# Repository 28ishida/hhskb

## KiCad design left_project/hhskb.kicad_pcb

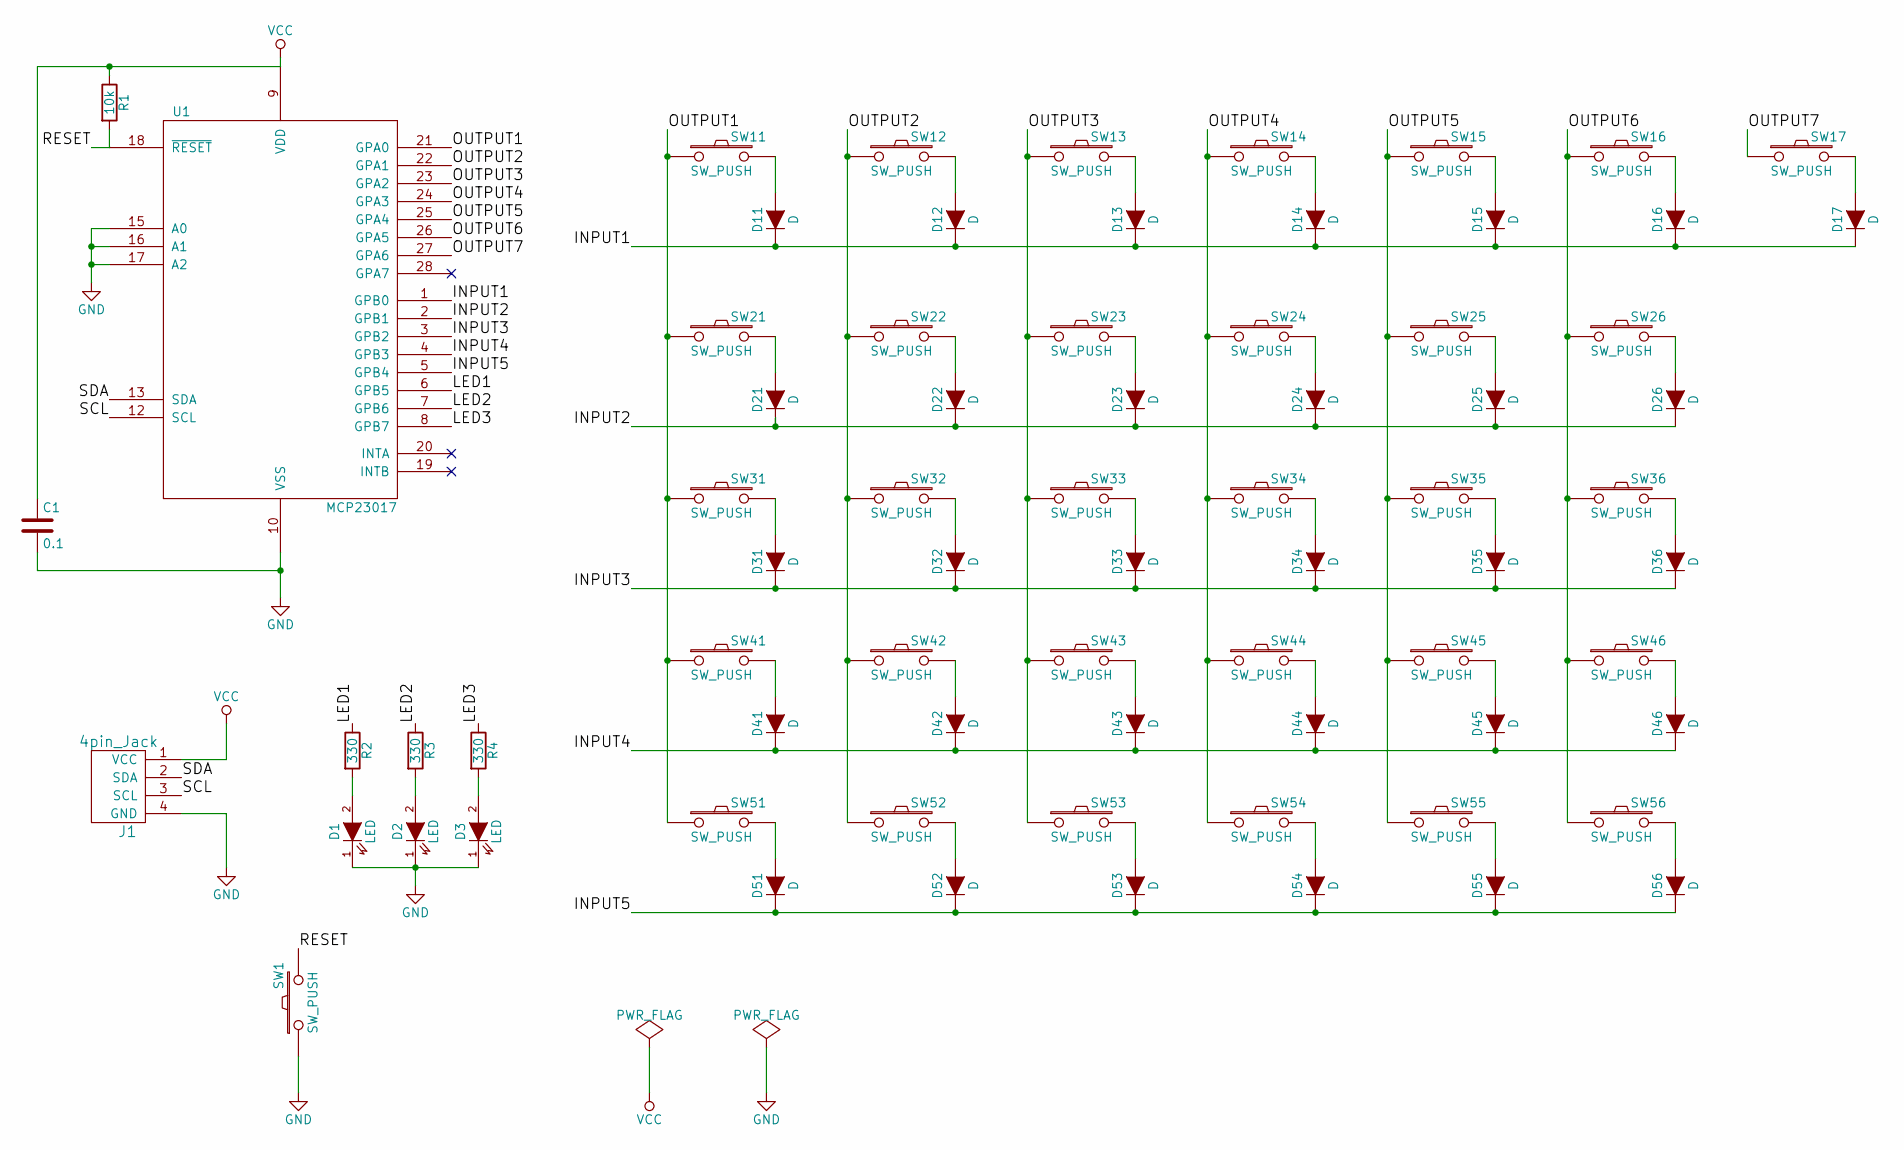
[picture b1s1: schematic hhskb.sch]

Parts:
C1: 0.1; C_Rect_L4.0mm_W2.5mm_P2.50mm
D1, D2, D3: LED; LED_D3.0mm
D11, D12, D13, D14, D15, D16, D17, D21, D22, D23, D24, D25, D26, D31, D32, D33, D34, D35, D36, D41, D42, D43, D44, D45, D46, D51, D52, D53, D54, D55, D56: D; DO-41
J1: 4pin_Jack
R1: 10k; R3-5
R2, R3, R4: 330; R3-5
SW1: SW_PUSH; tactswitch
SW11, SW12, SW13, SW14, SW15, SW16, SW17, SW22, SW23, SW24, SW25, SW26, SW32, SW33, SW34, SW35, SW36, SW42, SW43, SW44, SW45, SW46, SW52, SW53, SW54: SW_PUSH; CHERRY_PLATE_100H
SW21, SW55, SW56: SW_PUSH; CHERRY_PLATE_150H
SW31: SW_PUSH; CHERRY_PLATE_175H
SW41: SW_PUSH; CHERRY_PLATE_225H
SW51: SW_PUSH; CHERRY_PLATE_125H
U1: MCP23017; DIL28-3

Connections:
/INPUT1: D11.1 (K), D12.1 (K), D13.1 (K), D14.1 (K), D15.1 (K), D16.1 (K), D17.1 (K), U1.1 (GPB0)
/INPUT2: D21.1 (K), D22.1 (K), D23.1 (K), D24.1 (K), D25.1 (K), D26.1 (K), U1.2 (GPB1)
/INPUT3: D31.1 (K), D32.1 (K), D33.1 (K), D34.1 (K), D35.1 (K), D36.1 (K), U1.3 (GPB2)
/INPUT4: D41.1 (K), D42.1 (K), D43.1 (K), D44.1 (K), D45.1 (K), D46.1 (K), U1.4 (GPB3)
/INPUT5: D51.1 (K), D52.1 (K), D53.1 (K), D54.1 (K), D55.1 (K), D56.1 (K), U1.5 (GPB4)
/LED1: R2.1, U1.6 (GPB5)
/LED2: R3.1, U1.7 (GPB6)
/LED3: R4.1, U1.8 (GPB7)
/OUTPUT1: SW11.1, SW21.1, SW31.1, SW41.1, SW51.1, U1.21 (GPA0)
/OUTPUT2: SW12.1, SW22.1, SW32.1, SW42.1, SW52.1, U1.22 (GPA1)
/OUTPUT3: SW13.1, SW23.1, SW33.1, SW43.1, SW53.1, U1.23 (GPA2)
/OUTPUT4: SW14.1, SW24.1, SW34.1, SW44.1, SW54.1, U1.24 (GPA3)
/OUTPUT5: SW15.1, SW25.1, SW35.1, SW45.1, SW55.1, U1.25 (GPA4)
/OUTPUT6: SW16.1, SW26.1, SW36.1, SW46.1, SW56.1, U1.26 (GPA5)
/OUTPUT7: SW17.1, U1.27 (GPA6)
/RESET: R1.2, SW1.2, U1.18 (~RESET)
/SCL: J1.3 (SCL), U1.12 (SCL)
/SDA: J1.2 (SDA), U1.13 (SDA)
GND: C1.2, D1.1 (K), D2.1 (K), D3.1 (K), J1.4 (GND), SW1.1, U1.10 (VSS), U1.15 (A0), U1.16 (A1), U1.17 (A2)
unnamed: D1.2 (A), R2.2
unnamed: D2.2 (A), R3.2
unnamed: D3.2 (A), R4.2
unnamed: D11.2 (A), SW11.2
unnamed: D12.2 (A), SW12.2
unnamed: D13.2 (A), SW13.2
unnamed: D14.2 (A), SW14.2
unnamed: D15.2 (A), SW15.2
unnamed: D16.2 (A), SW16.2
unnamed: D17.2 (A), SW17.2
unnamed: D21.2 (A), SW21.2
unnamed: D22.2 (A), SW22.2
unnamed: D23.2 (A), SW23.2
unnamed: D24.2 (A), SW24.2
unnamed: D25.2 (A), SW25.2
unnamed: D26.2 (A), SW26.2
unnamed: D31.2 (A), SW31.2
unnamed: D32.2 (A), SW32.2
unnamed: D33.2 (A), SW33.2
unnamed: D34.2 (A), SW34.2
unnamed: D35.2 (A), SW35.2
unnamed: D36.2 (A), SW36.2
unnamed: D41.2 (A), SW41.2
unnamed: D42.2 (A), SW42.2
unnamed: D43.2 (A), SW43.2
unnamed: D44.2 (A), SW44.2
unnamed: D45.2 (A), SW45.2
unnamed: D46.2 (A), SW46.2
unnamed: D51.2 (A), SW51.2
unnamed: D52.2 (A), SW52.2
unnamed: D53.2 (A), SW53.2
unnamed: D54.2 (A), SW54.2
unnamed: D55.2 (A), SW55.2
unnamed: D56.2 (A), SW56.2
VCC: C1.1, J1.1 (VCC), R1.1, U1.9 (VDD)

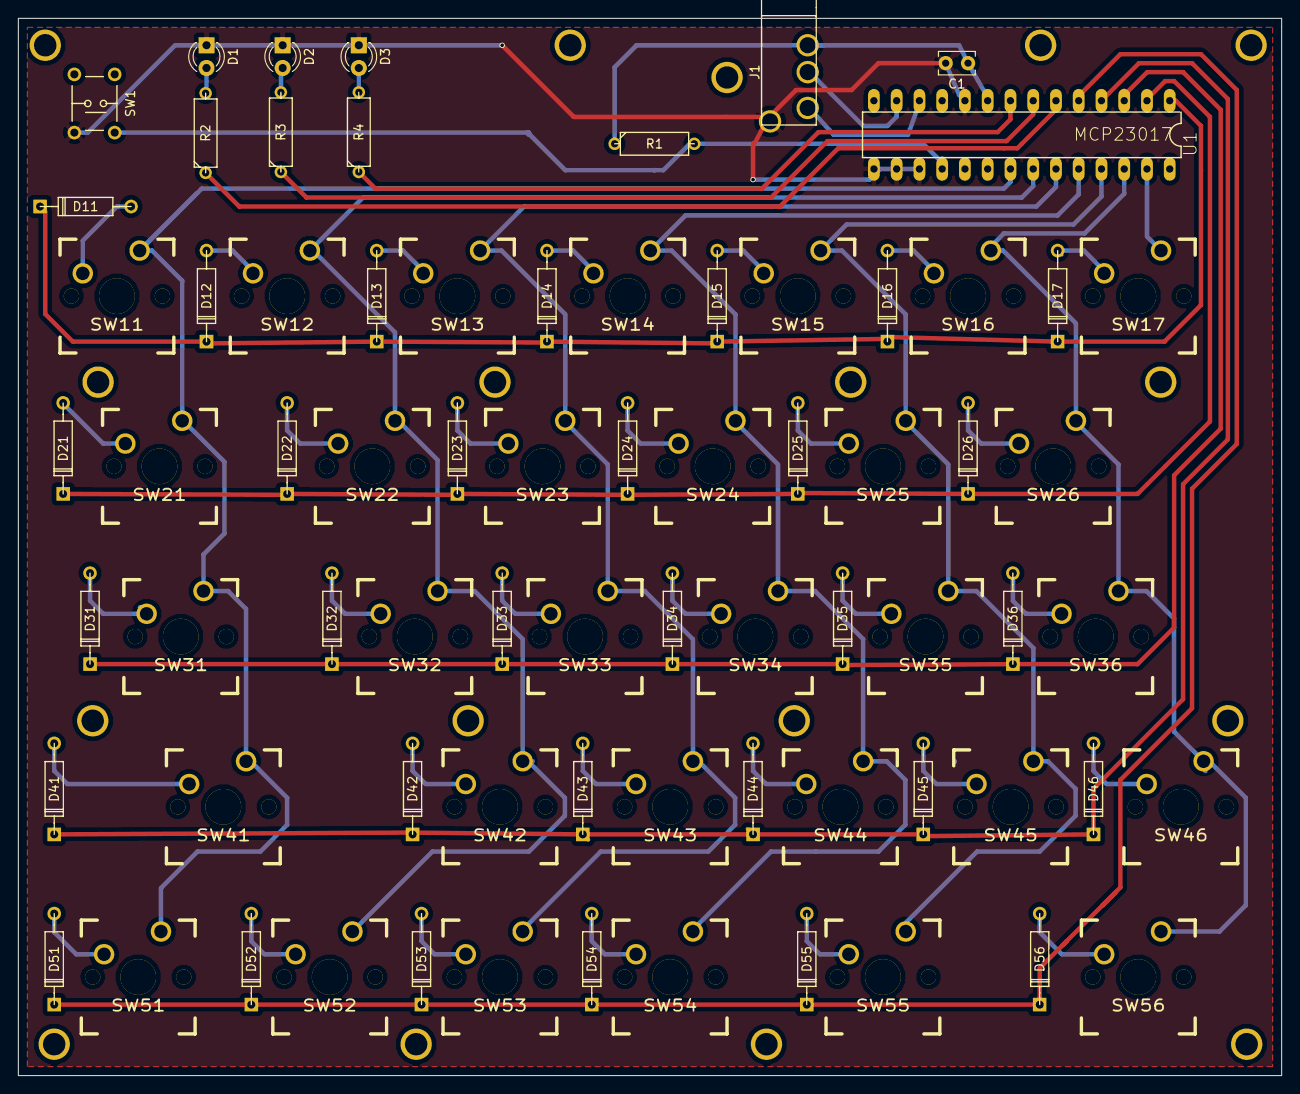
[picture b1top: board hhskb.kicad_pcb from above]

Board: 2 copper layers, 141.0 x 118.0 mm, 73 parts (0 on the bottom side), 54 nets.

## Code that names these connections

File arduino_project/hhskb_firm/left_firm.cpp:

#include "left_firm.h"
#include <arduino.h>
#include <skMCP230.h>
#include <Wire.h>

#define LED1 GPB5
#define LED2 GPB6
#define LED3 GPB7

// デバイスの７ビットアドレス(0100A2A1A0)
#define MCP230_ADDRESS  0b0100000   // MCP23017のI2Cアドレス(A2=0,A1=0,A0=0)
skMCP230 expIO(MCP230_ADDRESS);        // MCP23017ライブラリの生成を行う

// 左手モジュールの初期化。一度だけ呼び出してください
void InitLeftFirm()
{
	// Ｉ２Ｃの初期化
	Wire.begin();                     // マスターとする
	// MCP23017の初期化(ピンは全て出力で初期化されます)
	expIO.Init();

	expIO.pinMode(GPA, GPA0, INPUT_PULLUP);
	expIO.pinMode(GPA, GPA1, INPUT_PULLUP);
	expIO.pinMode(GPA, GPA2, INPUT_PULLUP);
	expIO.pinMode(GPA, GPA3, INPUT_PULLUP);
	expIO.pinMode(GPA, GPA4, INPUT_PULLUP);
	expIO.pinMode(GPA, GPA5, INPUT_PULLUP);
	expIO.pinMode(GPA, GPA6, INPUT_PULLUP);

	expIO.pinMode(GPB, GPB0, OUTPUT);
	expIO.pinMode(GPB, GPB1, OUTPUT);
	expIO.pinMode(GPB, GPB2, OUTPUT);
	expIO.pinMode(GPB, GPB3, OUTPUT);
	expIO.pinMode(GPB, GPB4, OUTPUT);

	expIO.Write(GPA, GPB0, HIGH);
	expIO.Write(GPA, GPB1, HIGH);
	expIO.Write(GPA, GPB2, HIGH);
	expIO.Write(GPA, GPB3, HIGH);
	expIO.Write(GPA, GPB4, HIGH);

	expIO.Write(GPB, LED1, HIGH);
	expIO.Write(GPB, LED2, LOW);
	expIO.Write(GPB, LED3, LOW);
}

// キーのパース 引数は5x7の行列分の領域を割り当て済である必要があります。
int ParseLeftKey(char ans[][8])
{
	unsigned char readbuf;
	char writebuf[8];
	memset(writebuf, -1, 8);

	unsigned char writebuf3;

	// 左手パース
	//expIO.Write(GPB, GPB0, LOW);
	
	//writebuf[4] = HIGH;
	//writebuf[0] = LOW;
	//expIO.Write2(GPB, writebuf);

	// この値がベースになる
	writebuf3 = expIO.Read(GPB);

	writebuf3 |= (0x01 << 4);
	writebuf3 &= ~(0x01 << 0);
	expIO.Write3(GPB, writebuf3);

	readbuf = expIO.Read(GPA);
	ans[0][0] = (readbuf >> GPA0) & 0x01;
	ans[0][1] = (readbuf >> GPA1) & 0x01;
	ans[0][2] = (readbuf >> GPA2) & 0x01;
	ans[0][3] = (readbuf >> GPA3) & 0x01;
	ans[0][4] = (readbuf >> GPA4) & 0x01;
	ans[0][5] = (readbuf >> GPA5) & 0x01;
	ans[0][6] = (readbuf >> GPA6) & 0x01;
	
	//expIO.Write(GPB, GPB0, HIGH);
	//expIO.Write(GPB, GPB1, LOW);
	//writebuf[0] = HIGH;
	//writebuf[1] = LOW;
	//expIO.Write2(GPB, writebuf);

	writebuf3 |= (0x01 << 0);
	writebuf3 &= ~(0x01 << 1);
	expIO.Write3(GPB, writebuf3);

	readbuf = expIO.Read(GPA);
	ans[1][0] = (readbuf >> GPA0) & 0x01;
	ans[1][1] = (readbuf >> GPA1) & 0x01;
	ans[1][2] = (readbuf >> GPA2) & 0x01;
	ans[1][3] = (readbuf >> GPA3) & 0x01;
	ans[1][4] = (readbuf >> GPA4) & 0x01;
	ans[1][5] = (readbuf >> GPA5) & 0x01;
	ans[1][6] = 0;
	//expIO.Write(GPB, GPB1, HIGH);
	//expIO.Write(GPB, GPB2, LOW);
	//writebuf[0] = -1;
	//writebuf[1] = HIGH;
	//writebuf[2] = LOW;
	//expIO.Write2(GPB, writebuf);
	writebuf3 |= (0x01 << 1);
	writebuf3 &= ~(0x01 << 2);
	expIO.Write3(GPB, writebuf3);

	readbuf = expIO.Read(GPA);
	ans[2][0] = (readbuf >> GPA0) & 0x01;
	ans[2][1] = (readbuf >> GPA1) & 0x01;
	ans[2][2] = (readbuf >> GPA2) & 0x01;
	ans[2][3] = (readbuf >> GPA3) & 0x01;
	ans[2][4] = (readbuf >> GPA4) & 0x01;
	ans[2][5] = (readbuf >> GPA5) & 0x01;
	ans[2][6] = 0;
	//expIO.Write(GPB, GPB2, HIGH);
	//expIO.Write(GPB, GPB3, LOW);
	//writebuf[1] = -1;
	//writebuf[2] = HIGH;
	//writebuf[3] = LOW;
	//expIO.Write2(GPB, writebuf);
	writebuf3 |= (0x01 << 2);
	writebuf3 &= ~(0x01 << 3);
	expIO.Write3(GPB, writebuf3);

	readbuf = expIO.Read(GPA);
	ans[3][0] = (readbuf >> GPA0) & 0x01;
	ans[3][1] = (readbuf >> GPA1) & 0x01;
	ans[3][2] = (readbuf >> GPA2) & 0x01;
	ans[3][3] = (readbuf >> GPA3) & 0x01;
	ans[3][4] = (readbuf >> GPA4) & 0x01;
	ans[3][5] = (readbuf >> GPA5) & 0x01;
	ans[3][6] = 0;
	//expIO.Write(GPB, GPB3, HIGH);
	//expIO.Write(GPB, GPB4, LOW);
	//writebuf[2] = -1;
	//writebuf[3] = HIGH;
	//writebuf[4] = LOW;
	//expIO.Write2(GPB, writebuf);
	writebuf3 |= (0x01 << 3);
	writebuf3 &= ~(0x01 << 4);
	expIO.Write3(GPB, writebuf3);

	readbuf = expIO.Read(GPA);
	ans[4][0] = (readbuf >> GPA0) & 0x01;
	ans[4][1] = (readbuf >> GPA1) & 0x01;
	ans[4][2] = (readbuf >> GPA2) & 0x01;
	ans[4][3] = (readbuf >> GPA3) & 0x01;
	ans[4][4] = (readbuf >> GPA4) & 0x01;
	ans[4][5] = (readbuf >> GPA5) & 0x01;
	ans[4][6] = 0;
	//expIO.Write(GPB, GPB4, HIGH);
}

int TurnOnStatusLed(int ledNum)
{
	if (ledNum == 0)
	{
		expIO.Write(GPB, LED1, HIGH);
	}
	else if (ledNum == 1)
	{
		expIO.Write(GPB, LED2, HIGH);
	}
	else if (ledNum == 2)
	{
		expIO.Write(GPB, LED3, HIGH);
	}
}
int TurnOffStatusLed(int ledNum)
{
	if (ledNum == 0)
	{
		expIO.Write(GPB, LED1, LOW);
	}
	else if (ledNum == 1)
	{
		expIO.Write(GPB, LED2, LOW);
	}
	else if (ledNum == 2)
	{
		expIO.Write(GPB, LED3, LOW);
	}
}

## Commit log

2017-02-02 最初の一歩
2017-02-04 プロジェクトを統合してフォルダ構成を変更
2017-02-04 キーレイアウト変更 * 一行目7キーを2つに分離 ** バックスラッシュとにょろで使う。 ** 二行目8キーはDeleteに変更 M2ねじのホール定義を変更 * 穴を2.5に変更 * ランドをねじ頭分3.5用意 ねじ穴を大量に用意
2017-02-05 4pinジャックのフットプリントを修正 ドリルの位置を微調整（明らかな直線は数字を合わせた）
2017-02-05 右手仕様書を最新設計に合わせた * 1行目8キーの追加 * 4行目hyper2の追加
2017-02-07 スイッチの穴をスルーホールに変更 * これでドリルファイルが一つにまとまる
    ガーバファイルの書き出し種類を変更。fusionの仕様に合わせた
2017-02-08 右手用で変更したライブラリを左に反映 左でしか使わないキーのサイズで穴をスルーホールに修正 ねじ穴をm2で2.5mm穴、レジスト付きに変更
2017-02-15 プレートのキャド図面の作成開始
    * まずは右手から
    * まだサイズマージンを入れてない
    * スタビライザーもまだ
    * ねじ穴＆外形もまだ
2017-02-19 背面プレート、スイッチ固定プレートの図面を作成中80% CADにプリント基板の絵をインポート成功 ネジの仕様書を追加
2017-02-20 スイッチ固定の穴を14mm -> 14.5mmに変更
2017-03-12 断面設計の見直し、アクリル製図をやり直し。
2017-04-05 左手用のプリント基板ガーバーデータをFix 右手用ケースアクリル設計情報を追加
2017-04-17 左手アクリル設計追加
2017-04-17 アクリルカット図面を準備 * アクリル板の交換回数で最適化済
2017-04-17 レーザカッター屋に出す設計図を用意
2017-05-04 左手アクリル設計の修正
2017-05-04 ファームデバッグ開始 プロジェクトを追加
2017-05-05 右手、左手それぞれキーをパースする部分をモジュールに分けでメインから切り離しました
2017-05-05 キーの連打認識までにディレイを入れました。
2017-05-06 一通り実装完了。
    * キーの自動リピートはPC側、USB周りで実装されているとのことでキーボードファームからは実装を抜きました
    * シリアルでの実験を終了。キーボードモジュールを使うよう修正
    * printは廃止。PressとReleaseで同時押しに堪えるように修正しました
    * 特殊キーは独自の定義を廃止。arduinoのライブラリ側で実装されてるらしいものを利用するよう修正しました
    * Fnキーの実装。
    ** Fnはオルタネイト動作にしました。これはHHKBとは異なる動作です。
2017-05-09 右GUIがWinキーにならないので、左GUIキーとして定義しました。 Fnをオルタネート動作はいろいろ不便な事も見えてきたので止め。
2017-05-12 修飾キーの左右がまちがっていたのを修正
2017-05-12 振り返り情報を追加
2017-05-26 すこしリファクタリング
2017-05-29 ポインタのポインタのインタフェースの廃止
    * 二次元配列を引数で指定できるように修正しました。
    * 無駄なポインタの定義がなくなってスッキリ。
2017-05-29 メインループをスッキリさせました。
    * キーコードを発火するのをメインループの外に持っていって
    * ファイル内広域変数をなるべく消去
2017-05-29 Fnと何かのキーを長時間同時押しした後、Fnキーのみを離した場合正しくreleaseキーコードが発射していなかった不具合を修正。
    * Fnをリリースした際はその時押下中のキーをすべてリセットする実装を入れました。
2017-05-30 Fn + Shift + 何か を押下して、Fnだけ離した場合にShiftがリリースされなくなる不具合を修正
2017-05-31 VisualStudioで開いて編集&アップデートしてみた。 今のところ問題無しに見えるが・・
2017-05-31 マジックナンバーを削除
2017-05-31 よけいなバイナリを削除
2017-05-31 無視リスト更新
2017-05-31 VS用のプロジェクトを追加
2017-05-31 VS用に無視リストを更新
2017-05-31 リファクタリング かなりスッキリ
2017-05-31 左コントロールにワンショットとしてスペースを割り当てた
2017-06-01 コメントの追加と、ワンショット処理の戻り値を戻していなかった不具合の修正
2017-06-01 Fnを離した際の処理の間違いを修正 左手だけFnと一緒に処理していたキーが単独押下として処理され続けてしまっていた
2017-06-20 ワンショットモディファイアにタイムアウトを導入
    * 押下して、一定時間がたつとワンショットをキャンセルするコードを実装
2017-06-20 コメントの追加
2017-08-15 ワンショットのキャンセル時にまれにジャグる事がある不具合の修正
2018-05-02 文字コードの変換。 arduino ideでビルドが通って、焼き込めるように修正
2018-05-08 キー定義の整理
2018-05-08 キーコード発射を一括処理に変更
    * ワンショットモディファーは無効中
2018-05-23 - ワンショットの実装変更 - 古い実装を削除 - レイヤ概念を追加 - キーマップを整理整頓 - 左右のパースの高速化 ー 左のパース高速化はライブラリを変更。ライブラリはコミットに含まれていない
2018-06-11 ワンショットリピートの修正実装
2018-06-11 skMCP230 をカスタマイズ
